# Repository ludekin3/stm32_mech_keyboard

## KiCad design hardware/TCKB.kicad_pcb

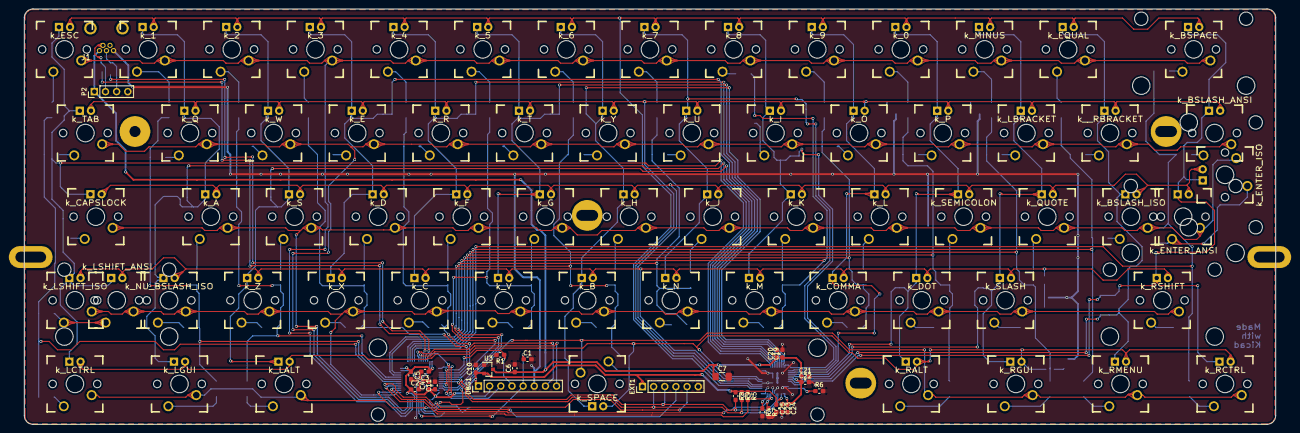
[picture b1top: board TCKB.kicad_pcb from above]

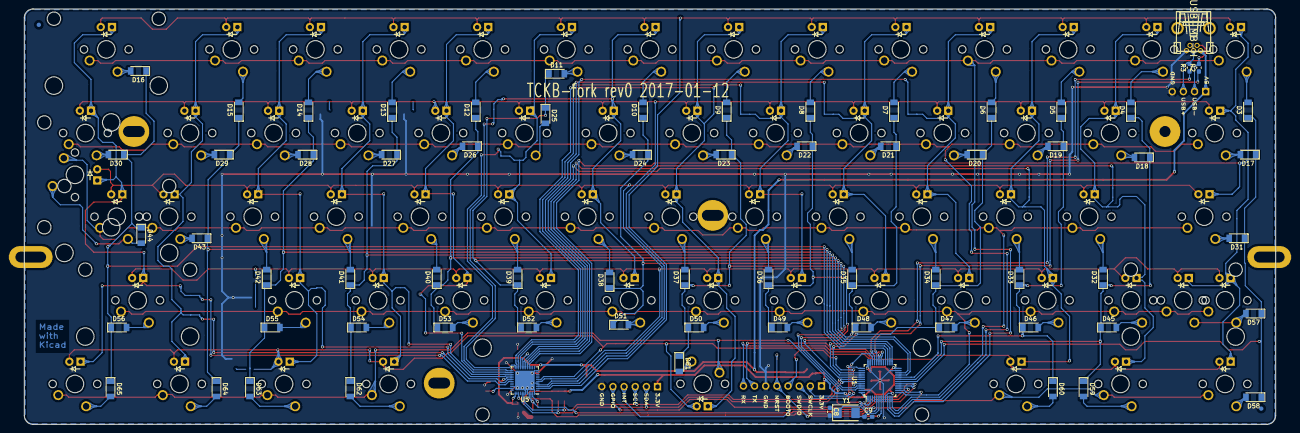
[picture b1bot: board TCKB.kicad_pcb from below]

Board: 2 copper layers, 285.0 x 94.6 mm, 242 parts (74 on the bottom side), 124 nets.

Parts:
C1, C2, C3, C4, C5, C11, C20, C21, C23: 100nF; C_0603_1608Metric_Pad1.05x0.95mm_HandSolder
C6, C10: 1uF; C_0603_1608Metric_Pad1.05x0.95mm_HandSolder
C7: 22uF; C_1206_3216Metric_Pad1.42x1.75mm_HandSolder
C8, C9: 22pF; C_0603_1608Metric_Pad1.05x0.95mm_HandSolder
C19, C22, C24, C25: 470nF; C_0603_1608Metric_Pad1.05x0.95mm_HandSolder
D3, D4, D5, D6, D7, D8, D9, D10, D11, D12, D13, D14, D15, D16, D17, D18, D19, D20, D21, D22, D23, D24, D25, D26, D27, D28, D29, D30, D31, D32, D33, D34, D35, D36, D37, D38, D39, D40, D41, D42, D43, D44, D45, D46, D47, D48, D49, D50, D51, D52, D53, D54, D55, D56, D57, D58, D59, D60, D61, D62, D63, D64, D65: 1N4148; D_MiniMELF
DBG1: STRIP_8P; PinHeader_1x08_P2.54mm_Vertical
EXT1: CONN_01X06; PinHeader_1x06_P2.54mm_Vertical
FID: FIDUCIAL
FID#2: FIDUCIAL
HOLE: VAL**; PKRHSL
HOLE#2: VAL**; PKRHSL
HOLE#3, HOLE#4, HOLE#5: VAL**; PKRH
HOLE#6: VAL**; PKRHC
J1: USB-MB-H
LED1: led_ESC; CHERRY_MX_LED
LED2: led_TAB; CHERRY_MX_LED
LED3: led_LSHIFT_ISO; CHERRY_MX_LED
LED4: led_LSHIFT_ANSI; CHERRY_MX_LED
LED5: led_LCTRL; CHERRY_MX_LED
LED6: led_1; CHERRY_MX_LED
LED7: led_Q; CHERRY_MX_LED
LED8: led_A; CHERRY_MX_LED
LED9: led_NU_BSLASH_ISO; CHERRY_MX_LED
LED10: led_LGUI; CHERRY_MX_LED
LED11: led_2; CHERRY_MX_LED
LED12: led_W; CHERRY_MX_LED
LED13: led_S; CHERRY_MX_LED
LED14: led_Z; CHERRY_MX_LED
LED15: led_LALT; CHERRY_MX_LED
LED16: led_3; CHERRY_MX_LED
LED17: led_E; CHERRY_MX_LED
LED18: led_D; CHERRY_MX_LED
LED19: led_X; CHERRY_MX_LED
LED20: led_4; CHERRY_MX_LED
LED21: led_R; CHERRY_MX_LED
LED22: led_F; CHERRY_MX_LED
LED23: led_C; CHERRY_MX_LED
LED24: led_5; CHERRY_MX_LED
LED25: led_T; CHERRY_MX_LED
LED26: led_G; CHERRY_MX_LED
LED27: led_V; CHERRY_MX_LED
LED28: led_6; CHERRY_MX_LED
LED29: led_Y; CHERRY_MX_LED
LED30: led_H; CHERRY_MX_LED
LED31: led_B; CHERRY_MX_LED
LED32: led_SPACE; CHERRY_MX_LED
LED33: led_7; CHERRY_MX_LED
LED34: led_U; CHERRY_MX_LED
LED35: led_J; CHERRY_MX_LED
LED36: led_N; CHERRY_MX_LED
LED37: led_8; CHERRY_MX_LED
LED38: led_I; CHERRY_MX_LED
LED39: led_K; CHERRY_MX_LED
LED40: led_M; CHERRY_MX_LED
LED41: led_9; CHERRY_MX_LED
LED42: led_O; CHERRY_MX_LED
LED43: led_L; CHERRY_MX_LED
LED44: led_COMMA; CHERRY_MX_LED
LED45: led_0; CHERRY_MX_LED
LED46: led_P; CHERRY_MX_LED
LED47: led_SEMICOLON; CHERRY_MX_LED
LED48: led_DOT; CHERRY_MX_LED
LED49: led_RALT; CHERRY_MX_LED
LED50: led_MINUS; CHERRY_MX_LED
LED51: led_LBRACKET; CHERRY_MX_LED
LED52: led_QUOTE; CHERRY_MX_LED
LED53: led_SLASH; CHERRY_MX_LED
LED54: led_RGUI; CHERRY_MX_LED
LED55: led_EQUAL; CHERRY_MX_LED
LED56: led_RBRACKET; CHERRY_MX_LED
LED57: led_BSLASH_ISO; CHERRY_MX_LED
LED58: led_RMENU; CHERRY_MX_LED
LED59: led_BSPACE; CHERRY_MX_LED
LED60: led_BSLASH_ANSI; CHERRY_MX_LED
LED61: led_ENTER_ISO; CHERRY_MX_LED
LED62: led_ENTER_ANSI; CHERRY_MX_LED
LED63: led_RSHIFT; CHERRY_MX_LED
LED64: led_RCTRL; CHERRY_MX_LED
LED65: led_CAPSLOCK; CHERRY_MX_LED
P2: CONN_01X04; PinHeader_1x04_P2.54mm_Vertical
R1: 220r; R_0603_1608Metric_Pad1.05x0.95mm_HandSolder
R2, R3: 22r; R_0603_1608Metric_Pad1.05x0.95mm_HandSolder
R4, R5, R7: 100k; R_0603_1608Metric_Pad1.05x0.95mm_HandSolder
R6: 20k; R_0603_1608Metric_Pad1.05x0.95mm_HandSolder
R8, R9: 1k; R_0603_1608Metric_Pad1.05x0.95mm_HandSolder
ST1: Backspace_2U; CHERRY_PCB_200H_STAB
ST2: ANSI_Return_2.25U; CHERRY_PCB_225H_STAB
ST3: ISO_Return_2U; CHERRY_PCB_200H_STAB
ST4: Right_Shift_2.75U; CHERRY_PCB_275H_STAB
ST5: ANSI_Left_Shift_2.25U; CHERRY_PCB_225H_STAB
ST6: Space_6.25U; CHERRY_PCB_625H_STAB
SW3: k_ESC; CHERRY_PCB_100H
SW4: k_1; CHERRY_PCB_100H
SW5: k_2; CHERRY_PCB_100H
SW6: k_3; CHERRY_PCB_100H
SW7: k_4; CHERRY_PCB_100H
SW8: k_5; CHERRY_PCB_100H
SW9: k_6; CHERRY_PCB_100H
SW10: k_7; CHERRY_PCB_100H
SW11: k_8; CHERRY_PCB_100H
SW12: k_9; CHERRY_PCB_100H
SW13: k_0; CHERRY_PCB_100H
SW14: k_MINUS; CHERRY_PCB_100H
SW15: k_EQUAL; CHERRY_PCB_100H
SW16: k_BSPACE; CHERRY_PCB_200H_SW
SW17: k_TAB; CHERRY_PCB_150H
SW18: k_Q; CHERRY_PCB_100H
SW19: k_W; CHERRY_PCB_100H
SW20: k_E; CHERRY_PCB_100H
SW21: k_R; CHERRY_PCB_100H
SW22: k_T; CHERRY_PCB_100H
SW23: k_Y; CHERRY_PCB_100H
SW24: k_U; CHERRY_PCB_100H
SW25: k_I; CHERRY_PCB_100H
SW26: k_O; CHERRY_PCB_100H
SW27: k_P; CHERRY_PCB_100H
SW28: k_LBRACKET; CHERRY_PCB_100H
SW29: k__RBRACKET; CHERRY_PCB_100H
SW30: k_BSLASH_ANSI; CHERRY_PCB_150H
SW31: k_CAPSLOCK; CHERRY_PCB_175H
SW32: k_A; CHERRY_PCB_100H
SW33: k_S; CHERRY_PCB_100H
SW34: k_D; CHERRY_PCB_100H
SW35: k_F; CHERRY_PCB_100H
SW36: k_G; CHERRY_PCB_100H
SW37: k_H; CHERRY_PCB_100H
SW38: k_J; CHERRY_PCB_100H
SW39: k_K; CHERRY_PCB_100H
SW40: k_L; CHERRY_PCB_100H
SW41: k_SEMICOLON; CHERRY_PCB_100H
SW42: k_QUOTE; CHERRY_PCB_100H
SW43: k_BSLASH_ISO; CHERRY_PCB_100H
SW44: k_ENTER_ISO; CHERRY_PCB_200H_SW
SW45: k_ENTER_ANSI; CHERRY_PCB_225H_SW
SW46: k_LSHIFT_ISO; CHERRY_PCB_125H
SW47: k_NU_BSLASH_ISO; CHERRY_PCB_100H
SW48: k_Z; CHERRY_PCB_100H
SW49: k_X; CHERRY_PCB_100H
SW50: k_C; CHERRY_PCB_100H
SW51: k_V; CHERRY_PCB_100H
SW52: k_B; CHERRY_PCB_100H
SW53: k_N; CHERRY_PCB_100H
SW54: k_M; CHERRY_PCB_100H
SW55: k_COMMA; CHERRY_PCB_100H
SW56: k_DOT; CHERRY_PCB_100H
SW57: k_SLASH; CHERRY_PCB_100H
SW58: k_RSHIFT; CHERRY_PCB_275H_SW
SW59: k_LSHIFT_ANSI; CHERRY_PCB_225H_SW
SW60: k_LCTRL; CHERRY_PCB_125H
SW61: k_LGUI; CHERRY_PCB_125H
SW62: k_LALT; CHERRY_PCB_125H
SW63: k_SPACE; CHERRY_PCB_625H_SW
SW64: k_RALT; CHERRY_PCB_125H
SW65: k_RGUI; CHERRY_PCB_125H
SW66: k_RMENU; CHERRY_PCB_125H
SW67: k_RCTRL; CHERRY_PCB_125H
U1: STM32F042C6Tx; LQFP-48_7x7mm_P0.5mm
U3: MCP1700T-3002E/TT; SOT-23
U5: IS31FL3733; UQFN-48-1EP_6x6mm_P0.4mm_EP4.45x4.45mm
Y1: Crystal; Crystal_SMD_Abracon_ABM3-2Pin_5.0x3.2mm

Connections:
+3V3: C2.1, C3.1, C4.1, C5.1, C10.1, C11.1, C25.1, DBG1.1, EXT1.1, R5.1, R8.1, R9.1, U1.1, U1.9, U1.24, U1.36, U1.48, U3.2, U5.39
+5V: C6.1, C7.1, C19.1, C20.1, C21.1, C22.1, C23.1, C24.1, J1.VBUS, P2.1, U3.3, U5.20, U5.29, U5.37, U5.38
/Led_Controller/RSET: R6.1, U5.35
BOOT0: DBG1.4, R1.1, U1.44
Col_0_: D3.1, D17.1, D31.1, D57.1, D58.1, U1.18
Col_1_: D4.1, D18.1, D32.1, D45.1, D59.1, U1.19
Col_2_: D5.1, D19.1, D33.1, D46.1, D60.1, U1.20
Col_3_: D6.1, D20.1, D34.1, D47.1, U1.39
Col_4_: D7.1, D21.1, D35.1, D48.1, U1.40
Col_5_: D8.1, D22.1, D36.1, D49.1, U1.41
Col_6_: D9.1, D23.1, D37.1, D50.1, D61.1, U1.45
Col_7_: D10.1, D24.1, D38.1, D51.1, U1.46
Col_8_: D11.1, D25.1, D39.1, D52.1, U1.21
Col_9_: D12.1, D26.1, D40.1, D53.1, U1.22
Col_10_: D13.1, D27.1, D41.1, D54.1, D62.1, U1.25
Col_11_: D14.1, D28.1, D42.1, D55.1, D63.1, U1.26
Col_12_: D15.1, D29.1, D43.1, D64.1, U1.27
Col_13_: D16.1, D30.1, D44.1, D56.1, D65.1, U1.28
EXT_GPIO: EXT1.5, U1.2
EXT_INT: EXT1.4, U1.17
GNDPWR: C1.2, C2.2, C3.2, C4.2, C5.2, C6.2, C7.2, C8.2, C9.2, C10.2, C11.2, C19.2, C20.2, C21.2, C22.2, C23.2, C24.2, C25.2, DBG1.6, EXT1.6, J1.GND, P2.4, R1.2, R4.2, R6.2, R7.2, U1.8, U1.23, U1.35, U1.47, U3.1, U5.5, U5.12, U5.34, U5.43, U5.44, U5.48, U5.49
LED_COL_0: LED1.2, LED2.2, LED3.2, LED4.2, LED5.2, LED65.2, U5.16
LED_COL_1: LED6.2, LED7.2, LED8.2, LED9.2, LED10.2, U5.17
LED_COL_2: LED11.2, LED12.2, LED13.2, LED14.2, LED15.2, U5.18
LED_COL_3: LED16.2, LED17.2, LED18.2, LED19.2, U5.19
LED_COL_4: LED20.2, LED21.2, LED22.2, LED23.2, U5.21
LED_COL_5: LED24.2, LED25.2, LED26.2, LED27.2, U5.22
LED_COL_6: LED28.2, LED29.2, LED30.2, LED31.2, LED32.2, U5.23
LED_COL_7: LED33.2, LED34.2, LED35.2, LED36.2, U5.24
LED_COL_8: LED37.2, LED38.2, LED39.2, LED40.2, U5.25
LED_COL_9: LED41.2, LED42.2, LED43.2, LED44.2, U5.26
LED_COL_10: LED45.2, LED46.2, LED47.2, LED48.2, LED49.2, U5.27
LED_COL_11: LED50.2, LED51.2, LED52.2, LED53.2, LED54.2, U5.28
LED_COL_12: LED55.2, LED56.2, LED57.2, LED58.2, U5.30
LED_COL_13: LED59.2, LED60.2, LED61.2, LED62.2, LED63.2, LED64.2, U5.31
LED_INT: R5.2, U1.16, U5.45
LED_LINE_0: LED1.1, LED6.1, LED11.1, LED16.1, LED20.1, LED24.1, LED28.1, LED33.1, LED37.1, LED41.1, LED45.1, LED50.1, LED55.1, LED59.1, U5.2
LED_LINE_1: LED2.1, LED7.1, LED12.1, LED17.1, LED21.1, LED25.1, LED29.1, LED34.1, LED38.1, LED42.1, LED46.1, LED51.1, LED56.1, LED60.1, U5.3
LED_LINE_2: LED8.1, LED13.1, LED18.1, LED22.1, LED26.1, LED30.1, LED35.1, LED39.1, LED43.1, LED47.1, LED52.1, LED57.1, LED61.1, LED62.1, LED65.1, U5.4
LED_LINE_3: LED3.1, LED4.1, LED9.1, LED14.1, LED19.1, LED23.1, LED27.1, LED31.1, LED36.1, LED40.1, LED44.1, LED48.1, LED53.1, LED63.1, U5.6
LED_LINE_4: LED5.1, LED10.1, LED15.1, LED32.1, LED49.1, LED54.1, LED58.1, LED64.1, U5.7
LED_SHTDN: R7.1, U1.15, U5.46
Line_0_: SW3.2, SW4.2, SW5.2, SW6.2, SW7.2, SW8.2, SW9.2, SW10.2, SW11.2, SW12.2, SW13.2, SW14.2, SW15.2, SW16.2, U1.10
Line_1_: SW17.2, SW18.2, SW19.2, SW20.2, SW21.2, SW22.2, SW23.2, SW24.2, SW25.2, SW26.2, SW27.2, SW28.2, SW29.2, SW30.2, U1.11
Line_2_: SW31.2, SW32.2, SW33.2, SW34.2, SW35.2, SW36.2, SW37.2, SW38.2, SW39.2, SW40.2, SW41.2, SW42.2, SW43.2, SW44.2, SW45.2, U1.12
Line_3_: SW46.2, SW47.2, SW48.2, SW49.2, SW50.2, SW51.2, SW52.2, SW53.2, SW54.2, SW55.2, SW56.2, SW57.2, SW58.2, SW59.2, U1.13
Line_4_: SW60.2, SW61.2, SW62.2, SW63.2, SW64.2, SW65.2, SW66.2, SW67.2, U1.14
NRST: C1.1, DBG1.5, U1.7
unnamed: D3.2, SW3.1
unnamed: D4.2, SW4.1
unnamed: D5.2, SW5.1
unnamed: D6.2, SW6.1
unnamed: D7.2, SW7.1
unnamed: D8.2, SW8.1
unnamed: D9.2, SW9.1
unnamed: D10.2, SW10.1
unnamed: D11.2, SW11.1
unnamed: D12.2, SW12.1
unnamed: D13.2, SW13.1
unnamed: D14.2, SW14.1
unnamed: D15.2, SW15.1
unnamed: D16.2, SW16.1
unnamed: D17.2, SW17.1
unnamed: D18.2, SW18.1
unnamed: D19.2, SW19.1
unnamed: D20.2, SW20.1
unnamed: D21.2, SW21.1
unnamed: D22.2, SW22.1
unnamed: D23.2, SW23.1
unnamed: D24.2, SW24.1
unnamed: D25.2, SW25.1
unnamed: D26.2, SW26.1
unnamed: D27.2, SW27.1
unnamed: D28.2, SW28.1
unnamed: D29.2, SW29.1
unnamed: D30.2, SW30.1
unnamed: D31.2, SW31.1
unnamed: D32.2, SW32.1
unnamed: D33.2, SW33.1
unnamed: D34.2, SW34.1
unnamed: D35.2, SW35.1
unnamed: D36.2, SW36.1
unnamed: D37.2, SW37.1
unnamed: D38.2, SW38.1
unnamed: D39.2, SW39.1
unnamed: D40.2, SW40.1
unnamed: D41.2, SW41.1
unnamed: D42.2, SW42.1
unnamed: D43.2, SW43.1
unnamed: D44.2, SW44.1, SW45.1
unnamed: D45.2, SW47.1
unnamed: D46.2, SW48.1
unnamed: D47.2, SW49.1
unnamed: D48.2, SW50.1
unnamed: D49.2, SW51.1
unnamed: D50.2, SW52.1
unnamed: D51.2, SW53.1
unnamed: D52.2, SW54.1
unnamed: D53.2, SW55.1
unnamed: D54.2, SW56.1
unnamed: D55.2, SW57.1
unnamed: D56.2, SW58.1
unnamed: D57.2, SW46.1, SW59.1
unnamed: D58.2, SW60.1
unnamed: D59.2, SW61.1
unnamed: D60.2, SW62.1
unnamed: D61.2, SW63.1
unnamed: D62.2, SW64.1
unnamed: D63.2, SW65.1
unnamed: D64.2, SW66.1
unnamed: D65.2, SW67.1
unnamed: R2.1, U1.32
unnamed: R3.1, U1.33
unnamed: R4.1, U5.47
OSC_IN: C8.1, U1.5, Y1.1
OSC_OUT: C9.1, U1.6, Y1.2
SCL: EXT1.3, R8.2, U1.42, U5.42
SDA: EXT1.2, R9.2, U1.43, U5.41
SWCLK: DBG1.2, U1.37
SWDIO: DBG1.3, U1.34
USART_RX: DBG1.8, U1.31
USART_TX: DBG1.7, U1.30
USB_M: J1.D-, P2.2, R2.2
USB_P: J1.D+, P2.3, R3.2

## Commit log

2020-03-14 Rescue Map symbols
2020-05-04 Update fp-info-cache
2020-05-04 Update Led_Controller.sch-bak
2020-05-04 Update TCKB.sch-bak
2020-05-04 Create TCKB.kicad_pcb-bak
2020-05-04 Update Matrix.sch-bak
2020-05-04 Update Led_Matrix.sch-bak
